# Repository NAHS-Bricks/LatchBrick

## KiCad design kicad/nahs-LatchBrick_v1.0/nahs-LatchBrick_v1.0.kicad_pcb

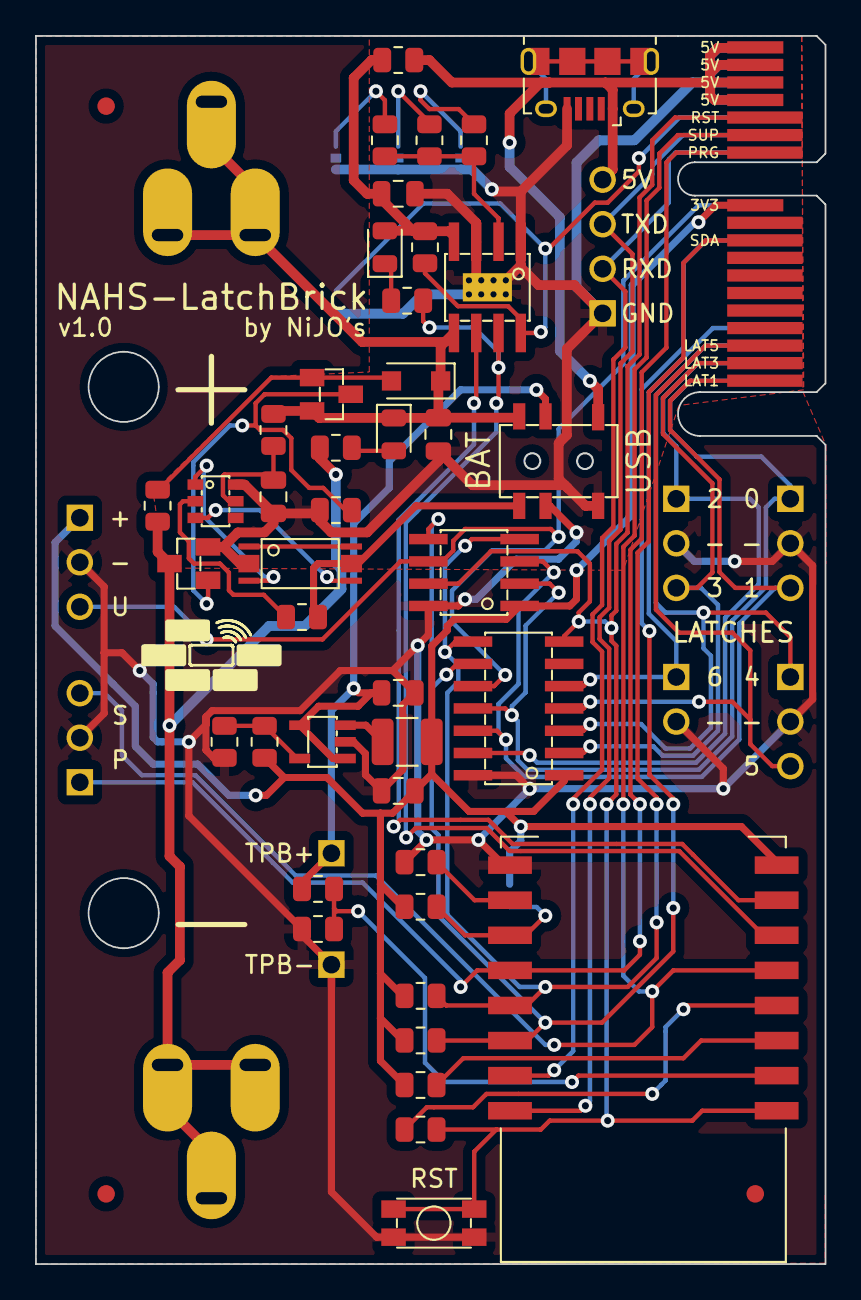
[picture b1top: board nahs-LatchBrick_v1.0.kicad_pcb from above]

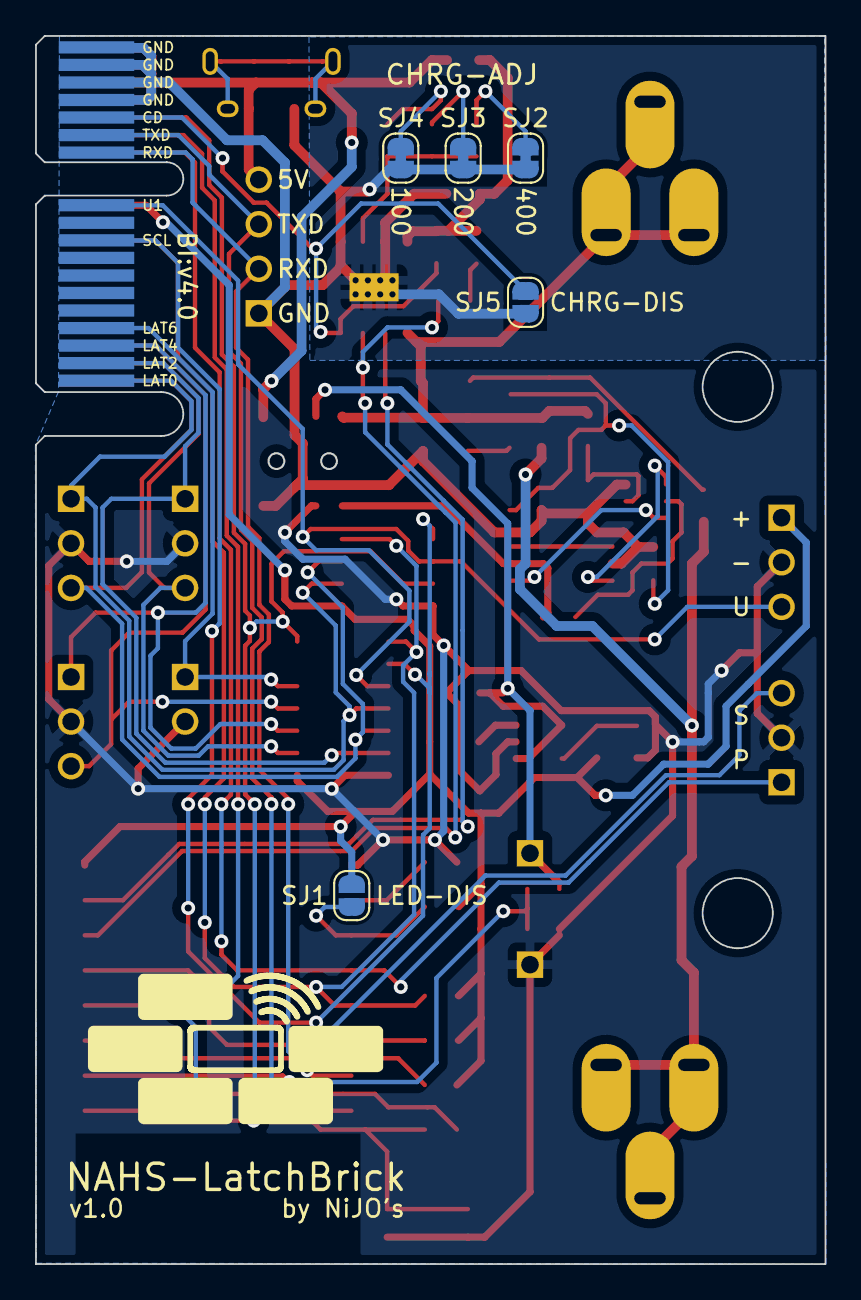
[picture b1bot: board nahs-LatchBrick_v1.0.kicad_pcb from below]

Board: 2 copper layers, 45.0 x 70.0 mm, 63 parts (6 on the bottom side), 47 nets.

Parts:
BT: HA_18650_EK
C1, C1#2, C1#3, C1#4, C1#5: 100nF; C_0805_2012Metric
D1: 1N4148WL; D_SOD-123F
FID1, FID2, FID3: Fiducial; Fiducial_1mm_Mask2mm
IC1: ESP12S
IC3: ATTINY414; SOIC14
IC?: ATTINY212; SOIC8
J: Brick-Interface-V4; Brick_Interface_V4_inset
J2: USB_B_Mini; USB_Micro-B_Amphenol_10118194_Horizontal
JP1, JP5, JP6, JP7, JP8: PINHD_1X03; PINHD_1X03_2.54_1mm_Round
JP2: PINHD_1X04; PINHD_1X04_2.54_1mm_Round
JP3, JP4: PINHD_1X01; PINHD_1X01_2.54_1mm_Square
JP9: PINHD_1x02; PINHD_1X02_2.54_1mm_Round
L1: 2.2µH; L_1210_3225Metric
LED1: Green; LED_0805_2012Metric
LED2: Red; LED_0805_2012Metric
LOGO1: brick_logo; x8mm
LOGO2: brick_logo; x17mm
Q1: 8205A; TSSOP8_MS
Q3: CJ2302; SOT23
Q4: MMBT2907A; SOT23
R2, R11, R14, R17: 1k; R_0805_2012Metric
R3, R4, R7, R13, R18, R19: 10k; R_0805_2012Metric
R5, R6: 3.9k; R_0805_2012Metric
R8: 2.7M; R_0805_2012Metric
R9, R21: 590k; R_0805_2012Metric
R10: 100; R_0805_2012Metric
R12: 0.4; R_0805_2012Metric
R15: 3k; R_0805_2012Metric
R20: 130k; R_0805_2012Metric
R22: 6,04k; R_0805_2012Metric
R23: 12k; R_0805_2012Metric
SJ1, SJ1#3, SJ1#5: RHT-ALT; SolderJumper-2_P1.3mm_Bridged_RoundedPad1.0x1.5mm
SJ1#2, SJ1#4: LED-DIS; SolderJumper-2_P1.3mm_Open_RoundedPad1.0x1.5mm
SW1: KMR_231_G_LFS
SW2: SSSS820101
U1: ZD8028IB5TR; SOT23-5
U3: DW01A; SOT23-6
U4: TP4056; SOIC8_TP

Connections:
+3V3: C1#3.1, IC1.8 (VCC), IC3.1 (VCC), IC?.1 (VCC), J.B11 (3.3V), JP5.1, L1.2, R3.1, R4.1, R5.1, R6.1, R21.2, SJ1#4.1 (A)
/CHRG+: C1.1, LED1.2 (A), R12.1, R13.1, U4.4 (VCC)
A0: IC1.2 (ADC), R8.2, R9.1
BAT+: BT.P (+), C1#4.1, D1.1 (K), LED2.1 (K), Q4.2 (E), R10.2, SW2.6, U4.5 (BAT)
BAT-: BT.M (-), Q3.3 (D), R17.2, R19.1
BOOT1: IC1.17 (D4), R4.2, SJ1#4.2 (B)
BOOT2: IC1.16 (D8), R7.2
CD: J.A14 (CD), R13.2, SJ1#2.2 (B), U4.8 (CE)
CHRG: IC1.6 (D6), R14.2, U4.7 (CHRG)
EN: IC1.3 (EN), R3.2
GND: C1#2.2, C1#3.2, IC1.15 (GND), IC3.14 (GND), IC?.8 (GND), JP1.2, JP4.1, JP5.2, JP6.2, JP7.2, JP8.2, JP9.2, R7.1, R9.2, R20.1, SW1.1, SW1.2, SW2.2, U1.2 (GND)
IN+: J.B15 (5V), J.B16 (5V), J.B17 (5V), J.B18 (5V), J2.1 (VBUS), JP2.4, R12.2, SW2.4
IN-: C1.2, C1#4.2, C1#5.2, J.A15 (GND), J.A16 (GND), J.A17 (GND), J.A18 (GND), J2.5 (GND), JP2.1, Q1.2 (S1), Q3.2 (S), R18.1, SJ1.1 (A), SJ1#2.1 (A), SJ1#3.1 (A), SJ1#5.1 (A), SW2.3, U3.6 (GND), U4.1 (TEMP), U4.3 (GND), U4.T1 (GND), U4.T2 (GND), U4.T3 (GND), U4.T4 (GND), U4.T5 (GND), U4.T6 (GND), U4.T7 (GND), U4.T8 (GND)
LACTH4: IC3.3 (PA5), J.A3 (UTIL7), JP8.1
LACTH5: IC3.4 (PA6), J.B3 (UTIL3), JP8.3
LACTH6: IC3.5 (PA7), J.A4 (UTIL8), JP9.1
LATCH0: IC3.11 (PA1), IC?.2 (PA6), J.A1 (UTIL5), JP6.1
LATCH1: IC3.12 (PA2), IC?.3 (PA7), J.B1 (UTIL1), JP6.3
LATCH2: IC3.13 (PA3), J.A2 (UTIL6), JP7.1
LATCH3: IC3.2 (PA4), J.B2 (UTIL2), JP7.3
unnamed: C1#5.1, R10.1, U3.5 (VCC)
unnamed: D1.2 (A), Q4.1 (B), R19.2
unnamed: IC1.4 (D0), R2.1
unnamed: L1.1, U1.3 (SW)
unnamed: LED1.1 (K), R14.1
unnamed: LED2.2 (A), R17.1
unnamed: Q1.1 (D1), Q1.6 (D2)
unnamed: Q1.3 (G1), U3.1 (OD)
unnamed: Q1.4 (G2), U3.3 (OC)
unnamed: Q3.1 (G), Q4.3 (C), R18.2
unnamed: R11.2, U3.2 (CS)
unnamed: R15.1, SJ1.2 (B)
unnamed: R15.2, R22.2, R23.2, U4.2 (PROG)
unnamed: R20.2, R21.1, U1.5 (FB)
unnamed: R22.1, SJ1#3.2 (B)
unnamed: R23.1, SJ1#5.2 (B)
PROG: IC1.18 (D3), J.B12 (PROG), JP1.1
PRT-: Q1.5 (S2), R11.1, SW2.1
RST: IC1.1 (~RST), IC3.7 (PB2), IC?.7 (PA3), J.B14 (RST), R2.2, SW1.3, SW1.4
RXD: IC1.21 (RXD0), J.A12 (RX), JP2.2
SCL: IC1.20 (D1), IC3.9 (PB0), IC?.5 (PA2), J.A9 (SCL), R6.2
SDA: IC1.19 (D2), IC3.8 (PB1), IC?.4 (PA1), J.B9 (SDA), R5.2
SEL+: C1#2.1, JP3.1, R8.1, SW2.5, U1.1 (EN), U1.4 (IN)
SETUP: IC1.5 (D5), J.B13 (SETUP), JP1.3
STDBY: IC1.7 (D7), U4.6 (STDBY)
TXD: IC1.22 (TXD0), J.A13 (TX), JP2.3
UPDI: IC3.10 (RST/UPDI), IC?.6 (RST/UPDI), J.A11 (UPDI1), JP5.3

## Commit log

2020-10-21 mit arbeiten an board v1.0_r1 begonnen
2020-10-22 Board v1.0_R1 should allready be finished
2020-10-22 final touches on v1.0_R1 before sending if over to jlcpcb
2020-10-23 started of with programming MainIC and CoIC
2020-11-02 latch interrupts implemented
2020-11-15 implementierung des coic soweit fertig, sollte bereit für test sein
2020-11-17 started interface to coic in arduino
2020-12-30 first round of testing software
2021-01-02 having a twi-prototype working ready to reimplement coic firmware
2021-01-03 zwischenspeichern
2021-01-04 interface working partially, reads seem to be ok, writes have trouble
2021-01-04 i2c interface now working
2021-01-05 latches implemented
2021-01-05 first round of bugfixing
2021-01-06 looks like CoIC is now working as expected
2021-01-12 R2 des boards begonnen und softwaretesting
2021-01-16 saving
2021-01-17 looks like i got the CoIC stable
2021-01-18 komponenten mit kleineren bohrungen eingesetzt
2021-01-19 Finale Version von v1.0_r2, die an JLCPCB übermittelt wurde
2021-01-22 Added INTERRUPT_CTL to CoIC Code
2021-01-23 bugfix in changing interrupt_ctl
2021-02-23 Migration von Arduino zu PlatformIO; mplab prokejt in CoIC Lib verlagert; CoIC wird nun aus Lib verwendet
2021-02-23 BrickSetup testet nun den CoIC
2021-02-27 now using RTCmem lib for RuntimeData
2021-04-28 moved brick-firmware to modular layout
2021-08-10 v1.0 R3 Board done
2022-01-13 build-firmware invoker
2023-01-10 added LICENSE
2023-01-13 v1.0 R4 Board done
2023-11-16 the firmware is now on the latest schema
2024-01-11 v1.0 Board done
